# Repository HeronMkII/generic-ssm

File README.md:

# generic-ssm

KiCAD files to be used as a template when creating sub-system specific
PCBs.

## Instructions on using this repository as a template

First, clone this repository. Next, install [homebrew](https://brew.sh/) and run

```
$ brew install rename
```

In the root directory, run

```
$ ls . | rename -vs generic YOUR_SUBSYSTEM_NAME
```

For example, `rename -vs generic coms` creates files
`coms_ssm.kicad_pcb`, `coms_ssm.pro` and `coms_ssm.sch`.

Next, delete this git repository by running

```
$ rm -Rf .git/
```

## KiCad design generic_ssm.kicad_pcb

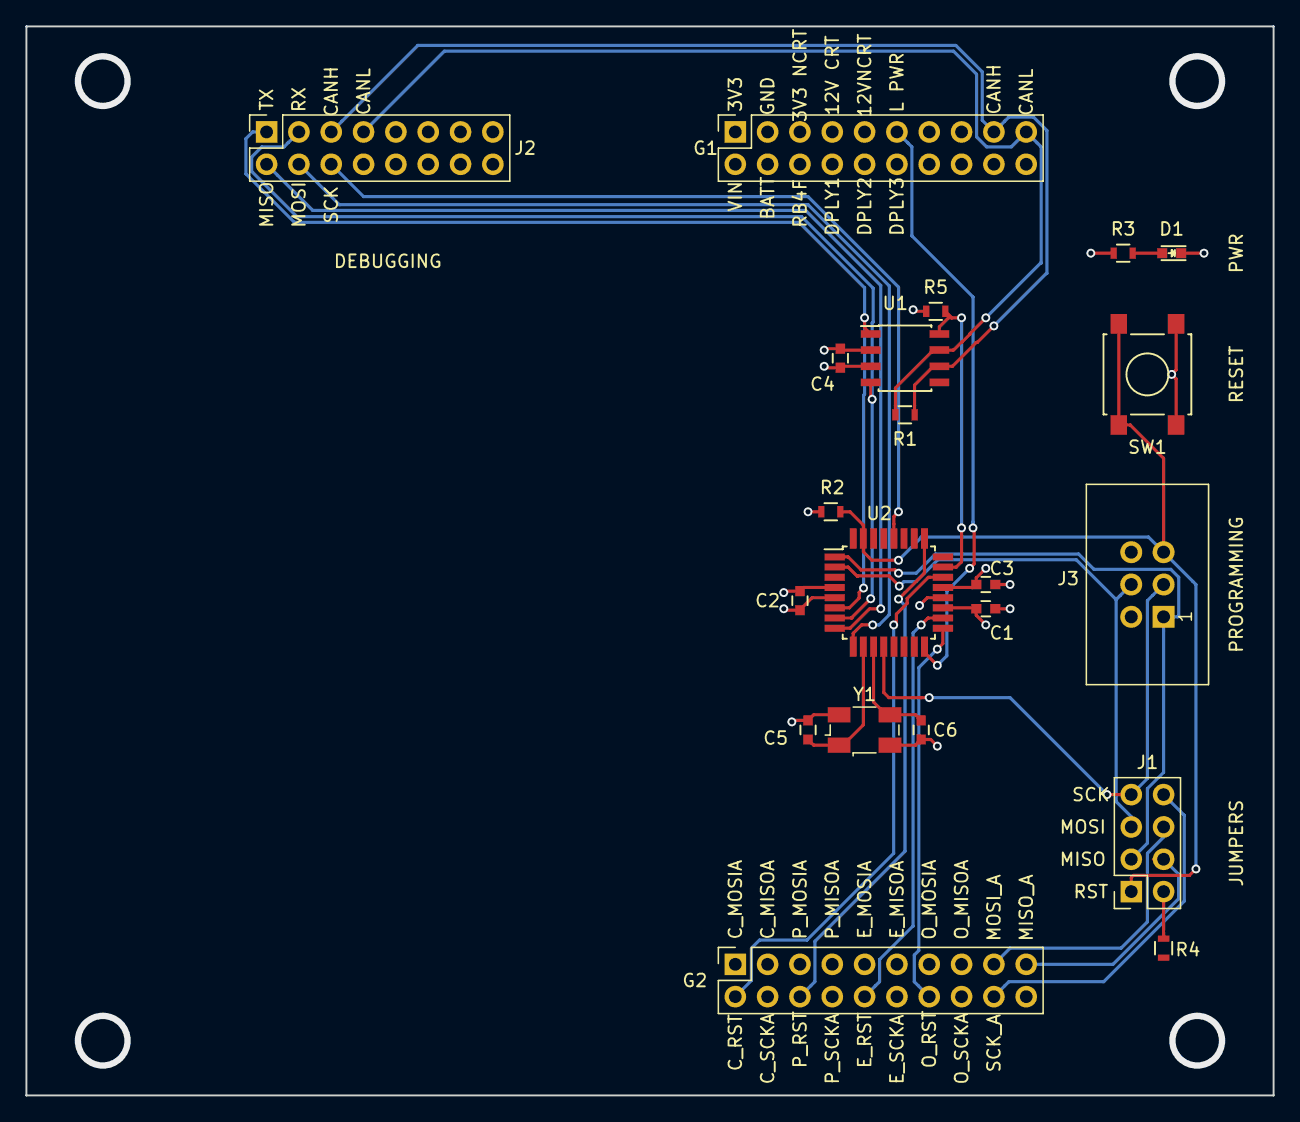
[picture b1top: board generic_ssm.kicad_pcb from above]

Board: 4 copper layers, 98.0 x 84.0 mm, 21 parts (0 on the bottom side), 26 nets.

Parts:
C1, C2, C3: 0.1 uF; C_0603
C4: 0.1uF; C_0603
C5, C6: 22pF; C_0603
D1: PWR_LED; LED_0603
G1: GENERAL CONN 1; Socket_Strip_Straight_2x10_Pitch2.54mm
G2: GENERAL CONN 2; Socket_Strip_Straight_2x10_Pitch2.54mm
J1: RST_JMP; Socket_Strip_Straight_2x04_Pitch2.54mm
J2: DEBUG CONN; Socket_Strip_Straight_2x08_Pitch2.54mm
J3: PROGRAMMING PORT; IDC_Header_Straight_6pins
R1, R3, R4: 120R; R_0603
R2: 10K; R_0603
R5: 1K; R_0603
SW1: SW_RST; SW_SPST_B3S-1000
U1: SN65HVD230; SOIC-8_3.9x4.9mm_Pitch1.27mm
U2: ATMEGA32M1-MU; TQFP-32_7x7mm_Pitch0.8mm
Y1: 8MHz; Crystal_SMD_Abracon_ABM3B-4pin_5.0x3.2mm

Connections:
+3V3: C1.2, C2.2, C3.2, C4.1, G1.1, J3.2, R2.1, R3.1, U1.3, U2.4, U2.19, U2.21
/CANH: G1.17, J2.5, R1.1, U1.7
/CANL: G1.19, J2.7, R1.2, U1.6
/CAN_LPWR: R5.2, U1.8, U2.23
/COM_RST: G2.2, U2.22
/EPS_RST: G2.10, U2.18
/LOPWR: G1.11, U2.16
/MISO: J2.2, U2.8
/MISO_A: J1.3, J3.1, U2.1
/MISO_A_COMMON: G2.19, J1.4
/MOSI: J2.4, U2.9
/MOSI_A: J1.5, J3.4, U2.2
/MOSI_A_COMMON: G2.17, J1.6
/OBC_RST: G2.14, U2.17
/PAY_RST: G2.6, U2.25
/RST: J1.1, J3.5, R2.2, SW1.1, U2.31
/RX_CAN: J2.3, U1.4, U2.7
/SCK: J2.6, U2.28
/SCK_A: J1.7, J3.3, U2.12
/SCK_A_COMMON: G2.18, J1.8
/TX_CAN: J2.1, U1.1, U2.6
GND: C1.1, C2.1, C3.1, C4.2, C5.1, C6.1, D1.1, G1.3, J3.6, R5.1, SW1.2, U1.2, U2.5, U2.20, Y1.2, Y1.4
unnamed: C5.2, U2.10, Y1.1
unnamed: C6.2, U2.11, Y1.3
unnamed: D1.2, R3.2
unnamed: J1.2, R4.2

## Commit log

2017-06-24 Rename files for consistency
2017-06-24 Created README.md
2017-06-24 Created TODO.md
2017-06-24 Corrected error in README.md
2017-08-13 Fixed for Flatsat 1
    Generic board. Read instructions on schematic to start building your
    own.
    Added G1, G2 common headers to stack boards on top of each other. Added
    standard debug header. Added power LED, reset pushbutton. Added
    decoupling caps on the power rails. Added jumper to enable/disable
    in-circuit reprogramming. Will think more about the reprogramming and
2017-08-16 Created the PCB schematic
2017-08-16 Ease-of-use changes to PCB routing.
2017-08-18 Minor Changes
    Fixed via sizes, fixed resistors on schematic
2017-08-18 Didn't save schematic properly last time
2017-08-18 Lo Power
    Added lo power input to 32m1 gpio pin, added can low power mode
    functionality for new can transceiver (hvd230)
2017-08-18 Minor fix
    deleted a no-connect
2017-08-18 Remade PCB layout for different header positions.
2017-08-18 Touched up the silkscreen.
2017-08-20 Bugfixes to the PCB layout.
2017-10-31 Fixed the layout of the CAN transciever.
2017-10-31 Updated PCB schematic with CAN fixes.
